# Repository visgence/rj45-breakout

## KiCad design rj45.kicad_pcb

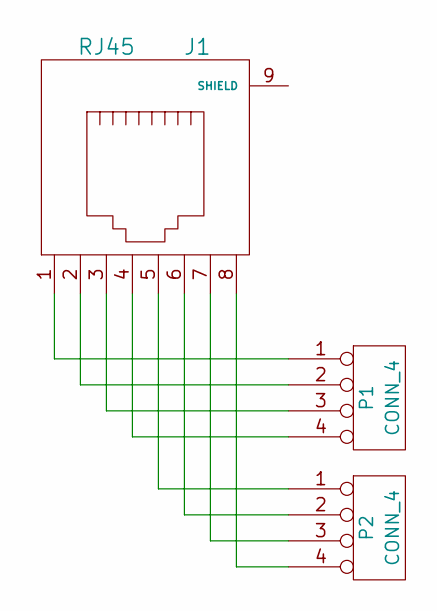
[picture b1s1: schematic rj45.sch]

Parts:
J1: RJ45
P1, P2: CONN_4

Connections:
unnamed: J1.5, P2.1
unnamed: J1.1, P1.1
unnamed: J1.2, P1.2
unnamed: J1.3, P1.3
unnamed: J1.4, P1.4
unnamed: J1.6, P2.2
unnamed: J1.7, P2.3
unnamed: J1.8, P2.4

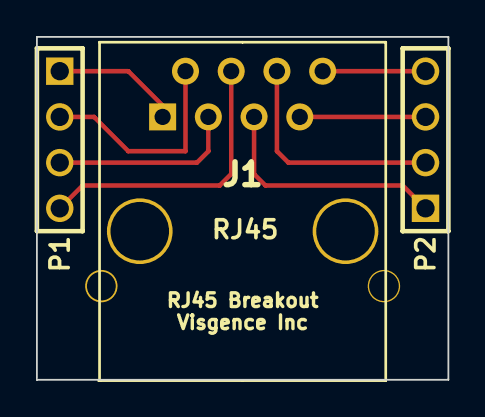
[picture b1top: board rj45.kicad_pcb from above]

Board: 2 copper layers, 22.9 x 19.1 mm, 3 parts (0 on the bottom side), 8 nets.

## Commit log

2016-06-07 Created RJ45 board.
2016-06-07 Changed file names
2016-06-14 Change origin for gerber generation
2018-07-07 adds dimensioned drawings of completed part
